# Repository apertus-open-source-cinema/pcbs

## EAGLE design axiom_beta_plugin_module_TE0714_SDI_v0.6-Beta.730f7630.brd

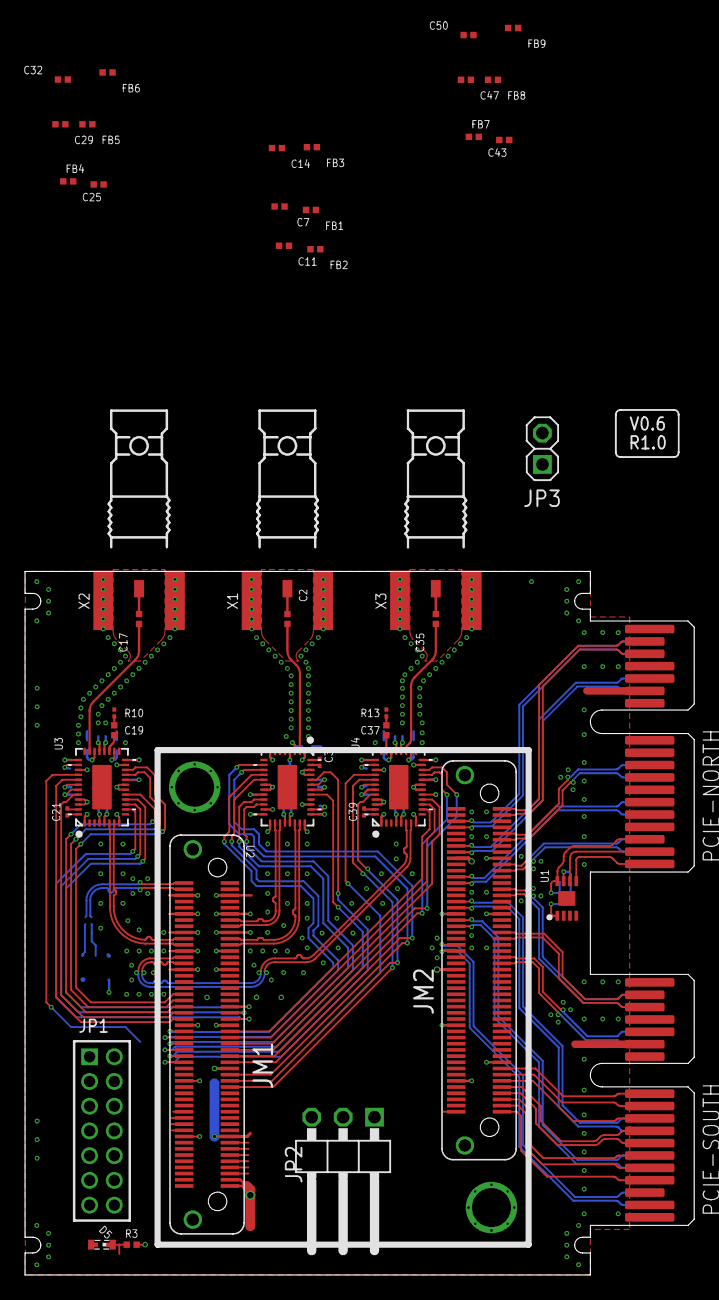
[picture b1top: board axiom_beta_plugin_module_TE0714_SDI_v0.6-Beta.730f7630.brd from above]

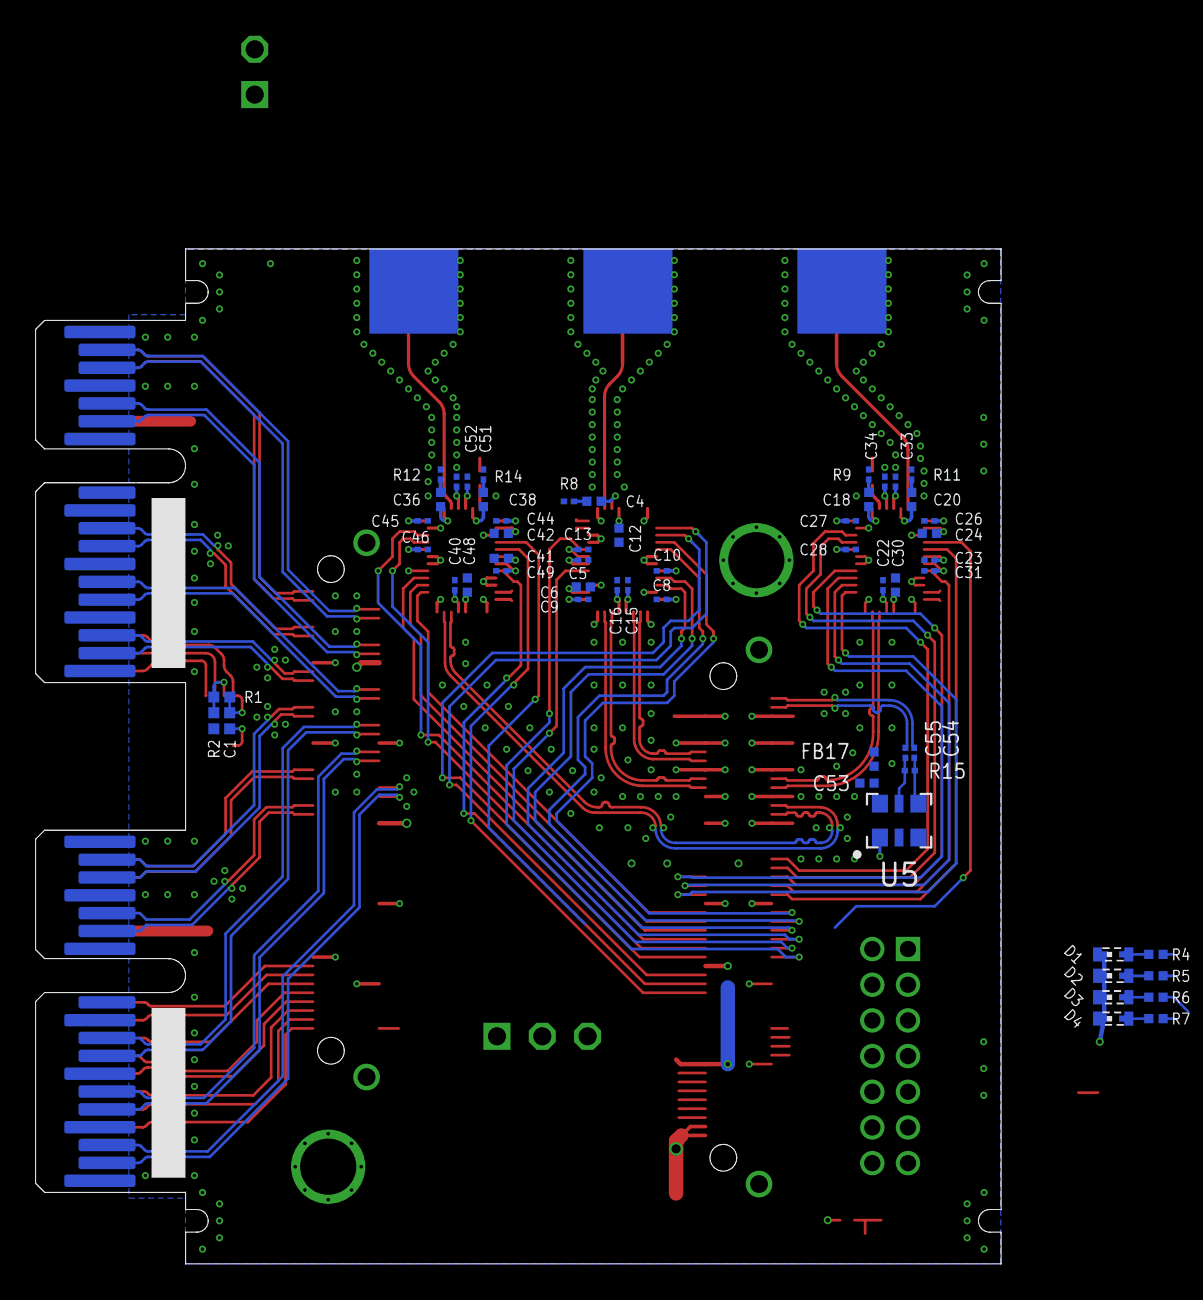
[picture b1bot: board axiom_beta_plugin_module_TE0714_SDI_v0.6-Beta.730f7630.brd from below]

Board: 4 copper layers, 54.1 x 56.9 mm, 101 parts (57 on the bottom side), 130 nets.

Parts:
C1: 0402-B
C2, C4, C17, C18, C19, C20, C35, C36, C37, C38: 4u7; 0402-C
C3, C21, C39: 470n; 0201-C
C5, C23: 10u; 0201-C
C6, C7, C11, C12, C14, C24, C25, C29, C30, C32, C41, C42, C43, C47, C48, C50: 10u; 0402-C
C8, C9, C10, C15, C16, C22, C26, C27, C28, C33, C34, C40, C44, C45, C46, C51, C52, C54, C55: 100n; 0201-C
C13, C31, C49: 1u; 0201-C
C53: 470n; 0402-C
D1, D2, D3, D4, D5: SMARTLED-TTW
FB1, FB2, FB3, FB4, FB5, FB6, FB7, FB8, FB9, FB17: 0402-C
JM1, JM2: LSHM-150-XX.X-XX-DV-A-S
JP1: 2X07M
JP2: 1X03/90-S
JP3: 1X02-S
LOGO2: OSHW_LOGO_FILLX0100-NT; OSHW_FILLX100_NOTEXT
PCIE-NORTH: PCIE-36-AXIOM
PCIE-SOUTH: PCIE-36-AXIOM
R1: 10k; 0402-B
R2: 1k; 0402-B
R3, R4, R5, R6, R7: 10k; 0402-C
R8: 0201-C
R9, R10, R11, R12, R13, R14: 75R; 0201-C
R15: 100R; 0201-C
U1: BR24G04NUX; DFN200X300X100-9N
U2: GS12241; UQFN40P600X400X100-41N
U3, U4: GS12281; UQFN40P600X400X100-41N
U5: DSC11XX-3.2X2.5; 3.2X2.5
X1, X2, X3: HDBNC; HDBNC_EDGE_2SIDE

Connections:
1V8: FB1.1, FB2.1, FB3.1, FB4.1, FB5.1, FB7.1, FB8.1, JM2.18
3V3: D1.A@1, D2.A@1, D3.A@1, D4.A@1, FB6.1, FB9.1, FB17.1, JM1.83, R3.2
B14_L0: JM2.99, PCIE-SOUTH.B4
B14_L17_N: JM2.89, PCIE-SOUTH.B9
B14_L17_P: JM2.91, PCIE-SOUTH.B8
B14_L18_N: JM2.85, PCIE-SOUTH.B11
B14_L18_P: JM2.87, PCIE-SOUTH.B10
B14_L20_N: JM2.95, PCIE-SOUTH.B6
B14_L20_P: JM2.93, PCIE-SOUTH.B7
B14_L21_N: JM1.95, U5.1
B14_L25: JM2.97, PCIE-SOUTH.B5
B15_L1_N: JM2.14, PCIE-NORTH.A14
B15_L1_P: JM2.16, PCIE-NORTH.A13
B15_L5_N: JM2.8, PCIE-NORTH.A16
B15_L5_P: JM2.6, PCIE-NORTH.A17
B15_L6_N: JM2.26, PCIE-NORTH.A5
B15_L6_P: JM2.24, PCIE-NORTH.A6
B15_L7_N: JM2.1, PCIE-NORTH.B17
B15_L7_P: JM2.3, PCIE-NORTH.B16
B15_L10_N: JM2.11, PCIE-NORTH.A8
B15_L10_P: JM2.9, PCIE-NORTH.A9
B15_L12_N: JM2.34, PCIE-SOUTH.A8
B15_L12_P: JM2.32, PCIE-SOUTH.A9
B15_L13_N: JM2.38, PCIE-SOUTH.A6
B15_L13_P: JM2.40, PCIE-SOUTH.A5
B15_L15_N: JM2.19, PCIE-NORTH.A3
B15_L15_P: JM2.21, PCIE-NORTH.A2
B15_L18_N: JM2.27, PCIE-SOUTH.A17
B15_L18_P: JM2.29, PCIE-SOUTH.A16
B15_L19_N: JM2.41, PCIE-SOUTH.B17
B15_L19_P: JM2.43, PCIE-SOUTH.B16
B15_L22_N: JM2.46, PCIE-SOUTH.A3
B15_L22_P: JM2.48, PCIE-SOUTH.A2
B15_L23_N: JM2.51, PCIE-SOUTH.A13
B15_L23_P: JM2.49, PCIE-SOUTH.A14
B34_L3_N: JM1.42, U3.13
B34_L3_P: JM1.40, U3.17
B34_L4_N: JM1.41, U3.12
B34_L5_N: JM1.45, U3.10
B34_L5_P: JM1.43, U3.11
B34_L7_N: JM1.38, U3.18
B34_L8_N: JM1.52, U2.13
B34_L8_P: JM1.50, U2.12
B34_L9_N: JM1.46, U3.33
B34_L9_P: JM1.44, U3.36
B34_L10_N: JM1.51, U4.11
B34_L10_P: JM1.49, U4.10
B34_L11_N: JM1.53, U4.12
B34_L11_P: JM1.55, U4.18
B34_L12_N: JM1.57, U4.17
B34_L12_P: JM1.59, U2.11
B34_L13_N: JM1.56, U2.18
B34_L13_P: JM1.54, U2.17
B34_L14_N: JM1.60, U2.36
B34_L14_P: JM1.58, U2.33
B34_L17_N: JM1.63, U2.10
B34_L17_P: JM1.65, U4.36
B34_L20_N: JM1.76, R4.1
B34_L20_P: JM1.78, R5.1
B34_L21_P: JM1.67, U4.33
B34_L24_N: JM1.80, R6.1
B34_L24_P: JM1.82, R7.1
BOOTMODE: JM2.100, JP3.1
DONE: D5.A@1, JM1.96, R3.1
GND: C1.2, C5.2, C6.2, C7.2, C8.2, C9.2, C10.2, C11.2, C12.2, C13.2, C14.2, C15.2, C16.2, C22.2, C23.2, C24.2, C25.2, C26.2, C27.2, C28.2, C29.2, C30.2, C31.2, C32.2, C33.2, C34.2, C40.2, C41.2, C42.2, C43.2, C44.2, C45.2, C46.2, C47.2, C48.2, C49.2, C50.2, C51.2, C52.2, C53.2, D5.C@1, JM1.5, JM1.6, JM1.11, JM1.12, JM1.17, JM1.18, JM1.23, JM1.24, JM1.29, JM1.30, JM1.47, JM1.48, JM1.66, JM1.84, JM1.98, JM1.100, JM1.F1, JM1.F2, JM2.17, JM2.35, JM2.36, JM2.72, JM2.83, JM2.90, JM2.F1, JM2.F2, JP2.1, JP3.2, PCIE-NORTH.A1, PCIE-NORTH.A4, PCIE-NORTH.A7, PCIE-NORTH.A10, PCIE-NORTH.A12, PCIE-NORTH.A15, PCIE-NORTH.A18, PCIE-NORTH.B15, PCIE-NORTH.B18, PCIE-SOUTH.A1, PCIE-SOUTH.A4, PCIE-SOUTH.A7, PCIE-SOUTH.A10, PCIE-SOUTH.A12, PCIE-SOUTH.A15, PCIE-SOUTH.A18, PCIE-SOUTH.B15, PCIE-SOUTH.B18, R2.2, R8.2, R9.2, R10.2, R11.2, R12.2, R13.2, R14.2, U1.1, U1.2, U1.3, U1.4, U1.EP, U2.1, U2.8, U2.14, U2.15, U2.19, U2.21, U2.28, U2.31, U2.37, U2.38, U3.1, U3.8, U3.14, U3.15, U3.19, U3.21, U3.28, U3.31, U3.37, U3.38, U4.1, U4.8, U4.14, U4.15, U4.19, U4.21, U4.28, U4.31, U4.37, U4.38, U5.3, X1.2@1, X1.2@2, X1.2@3, X2.2@1, X2.2@2, X2.2@3, X3.2@1, X3.2@2, X3.2@3
I2C_V: C1.1, PCIE-NORTH.B3, R1.1, U1.8
MGT_CLK0_N: C55.2, JM1.4
MGT_CLK0_P: C54.2, JM1.2
MGT_RX0_N: JM1.21, U2.27
MGT_RX0_P: JM1.19, U2.26
MGT_RX1_N: JM1.15, U2.23
MGT_RX1_P: JM1.13, U2.22
MGT_TX0_N: JM1.28, U4.6
MGT_TX0_P: JM1.26, U4.7
MGT_TX1_N: JM1.22, U3.6
MGT_TX1_P: JM1.20, U3.7
unnamed: D1.C@1, R4.2
unnamed: D2.C@1, R5.2
unnamed: D3.C@1, R6.2
unnamed: D4.C@1, R7.2
unnamed: C3.2, U2.40
unnamed: C3.1, U2.39
unnamed: C21.2, U3.40
unnamed: C21.1, U3.39
unnamed: C6.1, U2.30
unnamed: C5.1, U2.34
unnamed: C18.2, R9.1
unnamed: C18.1, U3.22
unnamed: C19.1, U3.23
unnamed: C19.2, R10.1
unnamed: C20.1, U3.26
unnamed: C20.2, R11.1
unnamed: C4.2, R8.1
unnamed: C4.1, U2.3
unnamed: C24.1, U3.30
unnamed: C23.1, U3.34
unnamed: C17.1, U3.27
unnamed: C22.1, U3.5
unnamed: C17.2, X2.1
unnamed: C35.1, U4.23
unnamed: C2.2, U2.2
unnamed: C2.1, X1.1
unnamed: C35.2, X3.1
unnamed: C39.2, U4.40
unnamed: C40.1, U4.5
unnamed: C41.1, U4.34
unnamed: C42.1, U4.30
unnamed: C38.2, R14.1
unnamed: C38.1, U4.26
unnamed: C37.2, R13.1
unnamed: C37.1, U4.27
unnamed: C36.1, U4.22
unnamed: C36.2, R12.1
unnamed: C39.1, U4.39
unnamed: R1.2, R2.1, U1.7
OUT_N: C55.1, R15.2, U5.5
OUT_P: C54.1, R15.1, U5.4
SCL: PCIE-NORTH.B2, U1.6
SDA: PCIE-NORTH.B1, U1.5
VCCO_4: C14.1, C15.1, C16.1, FB3.2, U2.24, U2.25
VCCO_8: C32.1, C33.1, C34.1, FB6.2, U3.24, U3.25
VCCO_9: C50.1, C51.1, C52.1, FB9.2, U4.24, U4.25
VCC_4: C11.1, C12.1, C13.1, FB2.2, U2.4, U2.35
VCC_8: C29.1, C30.1, C31.1, FB5.2, U3.4, U3.35
VCC_9: C47.1, C48.1, C49.1, FB8.2, U4.4, U4.35
VDD_4: C7.1, C8.1, C9.1, C10.1, FB1.2, U2.16, U2.20, U2.29
VDD_8: C25.1, C26.1, C27.1, C28.1, FB4.2, U3.16, U3.20, U3.29
VDD_9: C43.1, C44.1, C45.1, C46.1, FB7.2, U4.16, U4.20, U4.29
VIN: JM1.97, JM1.99, JP2.2
VXX: C53.1, FB17.2, U5.6

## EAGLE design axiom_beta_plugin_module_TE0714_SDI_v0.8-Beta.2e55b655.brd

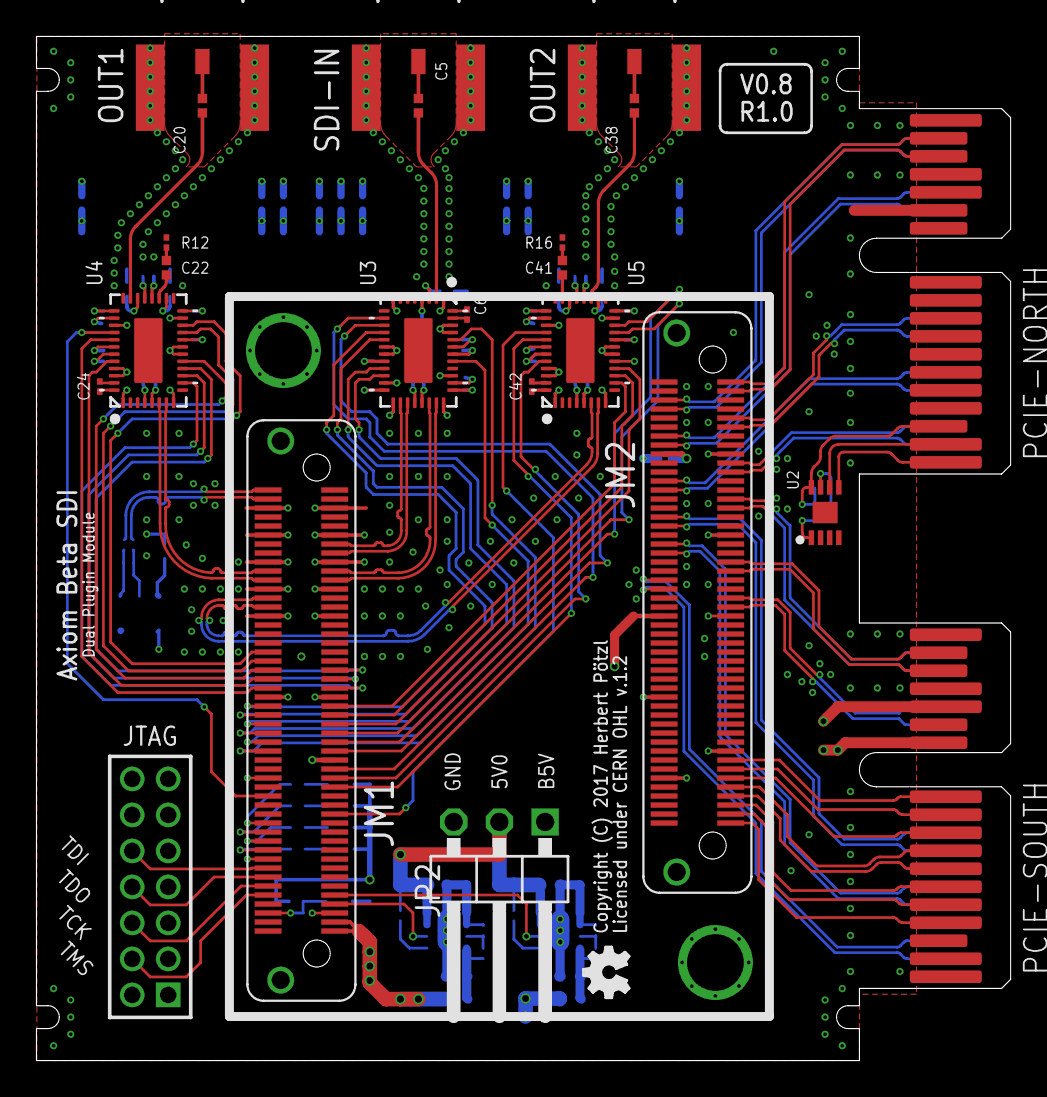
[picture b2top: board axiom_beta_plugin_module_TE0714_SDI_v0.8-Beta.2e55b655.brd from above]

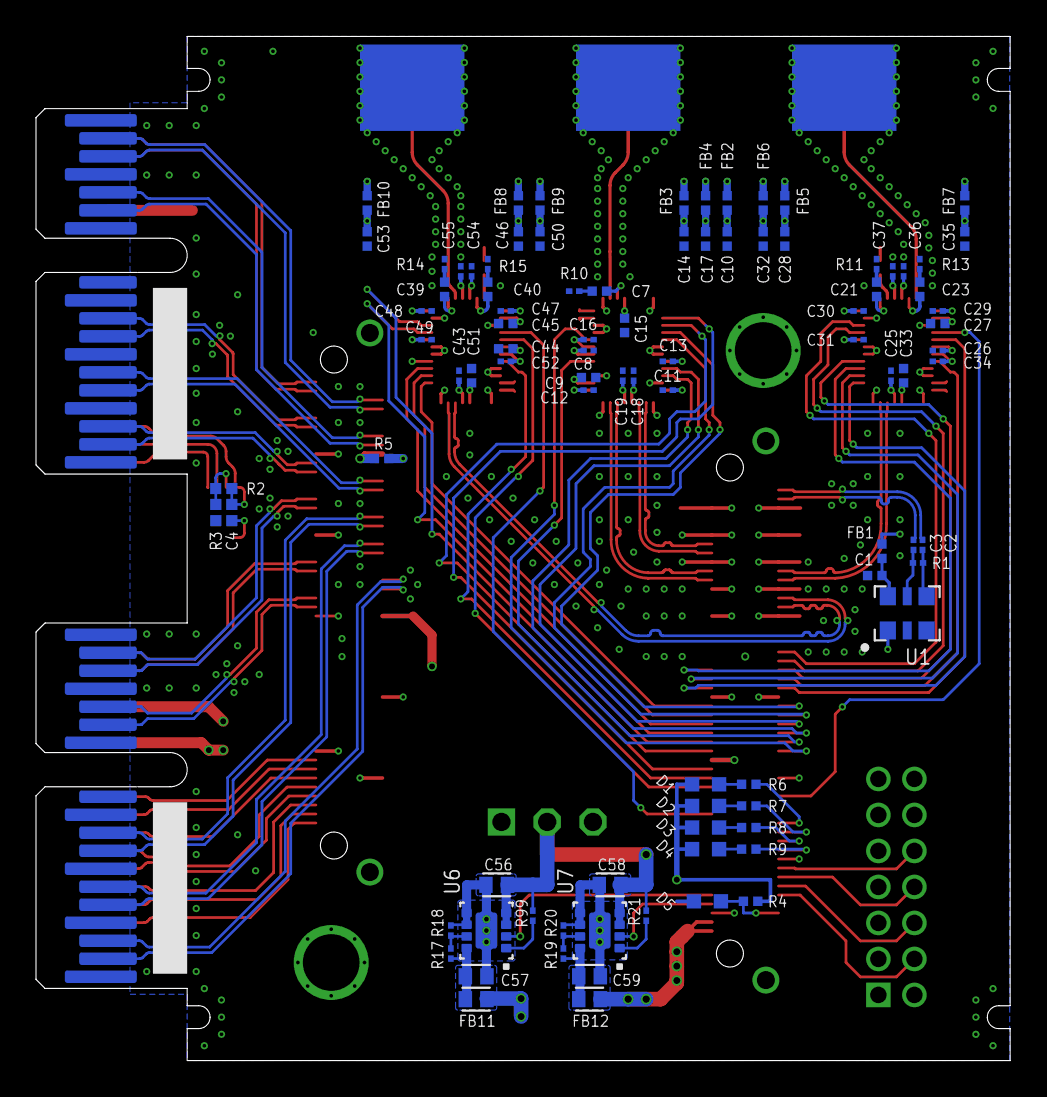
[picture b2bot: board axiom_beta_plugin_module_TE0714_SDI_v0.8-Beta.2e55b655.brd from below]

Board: 4 copper layers, 54.1 x 56.9 mm, 115 parts (91 on the bottom side), 147 nets.

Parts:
C1: 470n; 0402-C
C2, C3, C11, C12, C13, C18, C19, C25, C29, C30, C31, C36, C37, C43, C47, C48, C49, C54, C55: 100n; 0201-C
C4: 0402-B
C5, C7, C20, C21, C22, C23, C38, C39, C40, C41: 4u7; 0402-C
C6, C24, C42: 470n; 0201-C
C8, C26: 10u; 0201-C
C9, C10, C14, C15, C17, C27, C28, C32, C33, C35, C44, C45, C46, C50, C51, C53: 10u; 0402-C
C16, C34, C52: 1u; 0201-C
C56, C57, C58, C59: 0603-C
D1, D2, D3, D4, D5: LED; CHIPLED_0603
FB1, FB2, FB3, FB4, FB5, FB6, FB7, FB8, FB9, FB10: 0402-C
FB11, FB12: 0603-C
JM1, JM2: LSHM-150-XX.X-XX-DV-A-S
JP2: 1X03/90-S
JTAG: 2X07M
LOGO2: OSHW_LOGO_FILLX0100-NT; OSHW_FILLX100_NOTEXT
OUT1, OUT2: HDBNC; HDBNC_EDGE_2SIDE
PCIE-NORTH: PCIE-36-AXIOM
PCIE-SOUTH: PCIE-36-AXIOM
R1: 100R; 0201-C
R2: 10k; 0402-B
R3: 1k; 0402-B
R4, R6, R7, R8, R9: 10k; 0402-C
R5: 0R; 0402-C
R10, R17, R18, R19, R20: 0201-C
R11, R12, R13, R14, R15, R16: 75R; 0201-C
R21, R99: 10k; 0201-C
SDI-IN: HDBNC; HDBNC_EDGE_2SIDE
U1: DSC11XX-3.2X2.5; 3.2X2.5
U2: BR24G04NUX; DFN200X300X100-9N
U3: GS12241; UQFN40P600X400X100-41N
U4, U5: GS12281; UQFN40P600X400X100-41N
U6, U7: TPS82085; MICROSIP

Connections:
1V8: FB2.1, FB3.1, FB4.1, FB5.1, FB6.1, FB8.1, FB9.1, FB11.2, JM1.61, R5.1
3V3: D1.A, D2.A, D3.A, D4.A, FB1.1, FB7.1, FB10.1, FB12.2, JM1.97, JM1.99, R4.2
B14_L0: JM2.99, PCIE-SOUTH.B4
B14_L17_N: JM2.89, PCIE-SOUTH.B9
B14_L17_P: JM2.91, PCIE-SOUTH.B8
B14_L18_N: JM2.85, PCIE-SOUTH.B11
B14_L18_P: JM2.87, PCIE-SOUTH.B10
B14_L20_N: JM2.95, PCIE-SOUTH.B6
B14_L20_P: JM2.93, PCIE-SOUTH.B7
B14_L21_N: JM1.95, U1.1
B14_L21_P: JM1.93, U7.2
B14_L23_P: JM1.91, U6.2
B14_L25: JM2.97, PCIE-SOUTH.B5
B15_L1_N: JM2.14, PCIE-NORTH.A14
B15_L1_P: JM2.16, PCIE-NORTH.A13
B15_L5_N: JM2.8, PCIE-NORTH.A16
B15_L5_P: JM2.6, PCIE-NORTH.A17
B15_L6_N: JM2.26, PCIE-NORTH.A5
B15_L6_P: JM2.24, PCIE-NORTH.A6
B15_L7_N: JM2.1, PCIE-NORTH.B17
B15_L7_P: JM2.3, PCIE-NORTH.B16
B15_L10_N: JM2.11, PCIE-NORTH.A8
B15_L10_P: JM2.9, PCIE-NORTH.A9
B15_L12_N: JM2.34, PCIE-SOUTH.A8
B15_L12_P: JM2.32, PCIE-SOUTH.A9
B15_L13_N: JM2.38, PCIE-SOUTH.A6
B15_L13_P: JM2.40, PCIE-SOUTH.A5
B15_L15_N: JM2.19, PCIE-NORTH.A3
B15_L15_P: JM2.21, PCIE-NORTH.A2
B15_L18_N: JM2.27, PCIE-SOUTH.A17
B15_L18_P: JM2.29, PCIE-SOUTH.A16
B15_L19_N: JM2.41, PCIE-SOUTH.B17
B15_L19_P: JM2.43, PCIE-SOUTH.B16
B15_L22_N: JM2.46, PCIE-SOUTH.A3
B15_L22_P: JM2.48, PCIE-SOUTH.A2
B15_L23_N: JM2.51, PCIE-SOUTH.A13
B15_L23_P: JM2.49, PCIE-SOUTH.A14
B34_L3_N: JM1.42, U4.13
B34_L3_P: JM1.40, U4.17
B34_L4_N: JM1.41, U4.12
B34_L5_N: JM1.45, U4.10
B34_L5_P: JM1.43, U4.11
B34_L7_N: JM1.38, U4.18
B34_L8_N: JM1.52, U3.13
B34_L8_P: JM1.50, U3.12
B34_L9_N: JM1.46, U4.33
B34_L9_P: JM1.44, U4.36
B34_L10_N: JM1.51, U5.11
B34_L10_P: JM1.49, U5.10
B34_L11_N: JM1.53, U5.12
B34_L11_P: JM1.55, U5.17
B34_L12_N: JM1.57, U5.18
B34_L12_P: JM1.59, U3.11
B34_L13_N: JM1.56, U3.18
B34_L13_P: JM1.54, U3.17
B34_L14_N: JM1.60, U3.36
B34_L14_P: JM1.58, U3.33
B34_L16_P: JM1.70, U4.32
B34_L17_N: JM1.63, U3.10
B34_L17_P: JM1.65, U5.36
B34_L19_P: JM1.73, U5.32
B34_L20_N: JM1.76, R6.1
B34_L20_P: JM1.78, R7.1
B34_L21_P: JM1.67, U5.33
B34_L24_N: JM1.80, R8.1
B34_L24_P: JM1.82, R9.1
DONE: D5.A, JM1.96, R4.1
EN_A: R99.1, U6.1
EN_B: R21.1, U7.1
FB_A: R17.1, R18.2, U6.7
FB_B: R19.1, R20.2, U7.7
GND: C1.2, C4.2, C8.2, C9.2, C10.2, C11.2, C12.2, C13.2, C14.2, C15.2, C16.2, C17.2, C18.2, C19.2, C25.2, C26.2, C27.2, C28.2, C29.2, C30.2, C31.2, C32.2, C33.2, C34.2, C35.2, C36.2, C37.2, C43.2, C44.2, C45.2, C46.2, C47.2, C48.2, C49.2, C50.2, C51.2, C52.2, C53.2, C54.2, C55.2, C56.2, C57.2, C58.2, C59.2, D5.C, JM1.5, JM1.6, JM1.11, JM1.12, JM1.17, JM1.18, JM1.23, JM1.24, JM1.29, JM1.30, JM1.47, JM1.48, JM1.66, JM1.84, JM1.98, JM1.100, JM1.F1, JM1.F2, JM2.17, JM2.35, JM2.36, JM2.72, JM2.83, JM2.90, JM2.F1, JM2.F2, JP2.3, JTAG.1, JTAG.3, JTAG.5, JTAG.7, JTAG.9, JTAG.11, JTAG.13, OUT1.2@1, OUT1.2@2, OUT1.2@3, OUT2.2@1, OUT2.2@2, OUT2.2@3, PCIE-NORTH.A1, PCIE-NORTH.A4, PCIE-NORTH.A7, PCIE-NORTH.A10, PCIE-NORTH.A12, PCIE-NORTH.A15, PCIE-NORTH.A18, PCIE-NORTH.B15, PCIE-NORTH.B18, PCIE-SOUTH.A1, PCIE-SOUTH.A4, PCIE-SOUTH.A7, PCIE-SOUTH.A10, PCIE-SOUTH.A12, PCIE-SOUTH.A15, PCIE-SOUTH.A18, PCIE-SOUTH.B15, PCIE-SOUTH.B18, R3.2, R10.2, R11.2, R12.2, R13.2, R14.2, R15.2, R16.2, R18.1, R20.1, SDI-IN.2@1, SDI-IN.2@2, SDI-IN.2@3, U1.3, U2.1, U2.2, U2.3, U2.4, U2.EP, U3.1, U3.8, U3.14, U3.15, U3.19, U3.21, U3.28, U3.31, U3.37, U3.38, U4.1, U4.8, U4.14, U4.15, U4.19, U4.21, U4.28, U4.31, U4.37, U4.38, U5.1, U5.8, U5.14, U5.15, U5.19, U5.21, U5.28, U5.31, U5.37, U5.38, U6.5, U6.6, U6.EP, U7.5, U7.6, U7.EP
I2C_V: C4.1, PCIE-NORTH.B3, R2.1, U2.8
MGT_CLK0_N: C3.2, JM1.4
MGT_CLK0_P: C2.2, JM1.2
MGT_RX0_N: JM1.21, U3.27
MGT_RX0_P: JM1.19, U3.26
MGT_RX1_N: JM1.15, U3.23
MGT_RX1_P: JM1.13, U3.22
MGT_TX0_N: JM1.28, U5.6
MGT_TX0_P: JM1.26, U5.7
MGT_TX1_N: JM1.22, U4.6
MGT_TX1_P: JM1.20, U4.7
M_1V8: JM2.18, R5.2
unnamed: D1.C, R6.2
unnamed: D2.C, R7.2
unnamed: D3.C, R8.2
unnamed: D4.C, R9.2
unnamed: C6.2, U3.40
unnamed: C6.1, U3.39
unnamed: C24.2, U4.40
unnamed: C24.1, U4.39
unnamed: C9.1, U3.30
unnamed: C8.1, U3.34
unnamed: C21.2, R11.1
unnamed: C21.1, U4.22
unnamed: C22.1, U4.23
unnamed: C22.2, R12.1
unnamed: C23.1, U4.26
unnamed: C23.2, R13.1
unnamed: C7.2, R10.1
unnamed: C7.1, U3.3
unnamed: C27.1, U4.30
unnamed: C26.1, U4.34
unnamed: C20.1, U4.27
unnamed: C25.1, U4.5
unnamed: C20.2, OUT1.1
unnamed: C38.1, U5.23
unnamed: C5.2, U3.2
unnamed: C5.1, SDI-IN.1
unnamed: C38.2, OUT2.1
unnamed: C42.2, U5.40
unnamed: C43.1, U5.5
unnamed: C44.1, U5.34
unnamed: C45.1, U5.30
unnamed: C40.2, R15.1
unnamed: C40.1, U5.26
unnamed: C41.2, R16.1
unnamed: C41.1, U5.27
unnamed: C39.1, U5.22
unnamed: C39.2, R14.1
unnamed: C42.1, U5.39
unnamed: R2.2, R3.1, U2.7
OUT_N: C3.1, R1.2, U1.5
OUT_P: C2.1, R1.1, U1.4
SCL: PCIE-NORTH.B2, U2.6
SDA: PCIE-NORTH.B1, U2.5
S_5V: JP2.1, PCIE-SOUTH.B12
S_VCCIO: JM2.54, PCIE-SOUTH.B14
TCK: JM1.90, JTAG.6
TDI: JM1.86, JTAG.10
TDO: JM1.88, JTAG.8
TMS: JM1.92, JTAG.4
VCCIO0: JM2.53, JTAG.2
VCCO_4: C17.1, C18.1, C19.1, FB4.2, U3.24, U3.25
VCCO_8: C35.1, C36.1, C37.1, FB7.2, U4.24, U4.25
VCCO_9: C53.1, C54.1, C55.1, FB10.2, U5.24, U5.25
VCC_4: C14.1, C15.1, C16.1, FB3.2, U3.4, U3.35
VCC_8: C32.1, C33.1, C34.1, FB6.2, U4.4, U4.35
VCC_9: C50.1, C51.1, C52.1, FB9.2, U5.4, U5.35
VDD_4: C10.1, C11.1, C12.1, C13.1, FB2.2, U3.16, U3.20, U3.29
VDD_8: C28.1, C29.1, C30.1, C31.1, FB5.2, U4.16, U4.20, U4.29
VDD_9: C46.1, C47.1, C48.1, C49.1, FB8.2, U5.16, U5.20, U5.29
VOUT_A: C57.1, FB11.1, R17.2, U6.8
VOUT_B: C59.1, FB12.1, R19.2, U7.8
VSUP: C56.1, C58.1, JP2.2, R21.2, R99.2, U6.3, U6.4, U7.3, U7.4
VXX: C1.1, FB1.2, U1.6

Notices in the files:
axiom_beta_plugin_module_TE0714_SDI_v0.6-Beta.730f7630.brd:
Copyright (C) 2017 Herbert Pötzl
Licensed under CERN OHL v.1.2
